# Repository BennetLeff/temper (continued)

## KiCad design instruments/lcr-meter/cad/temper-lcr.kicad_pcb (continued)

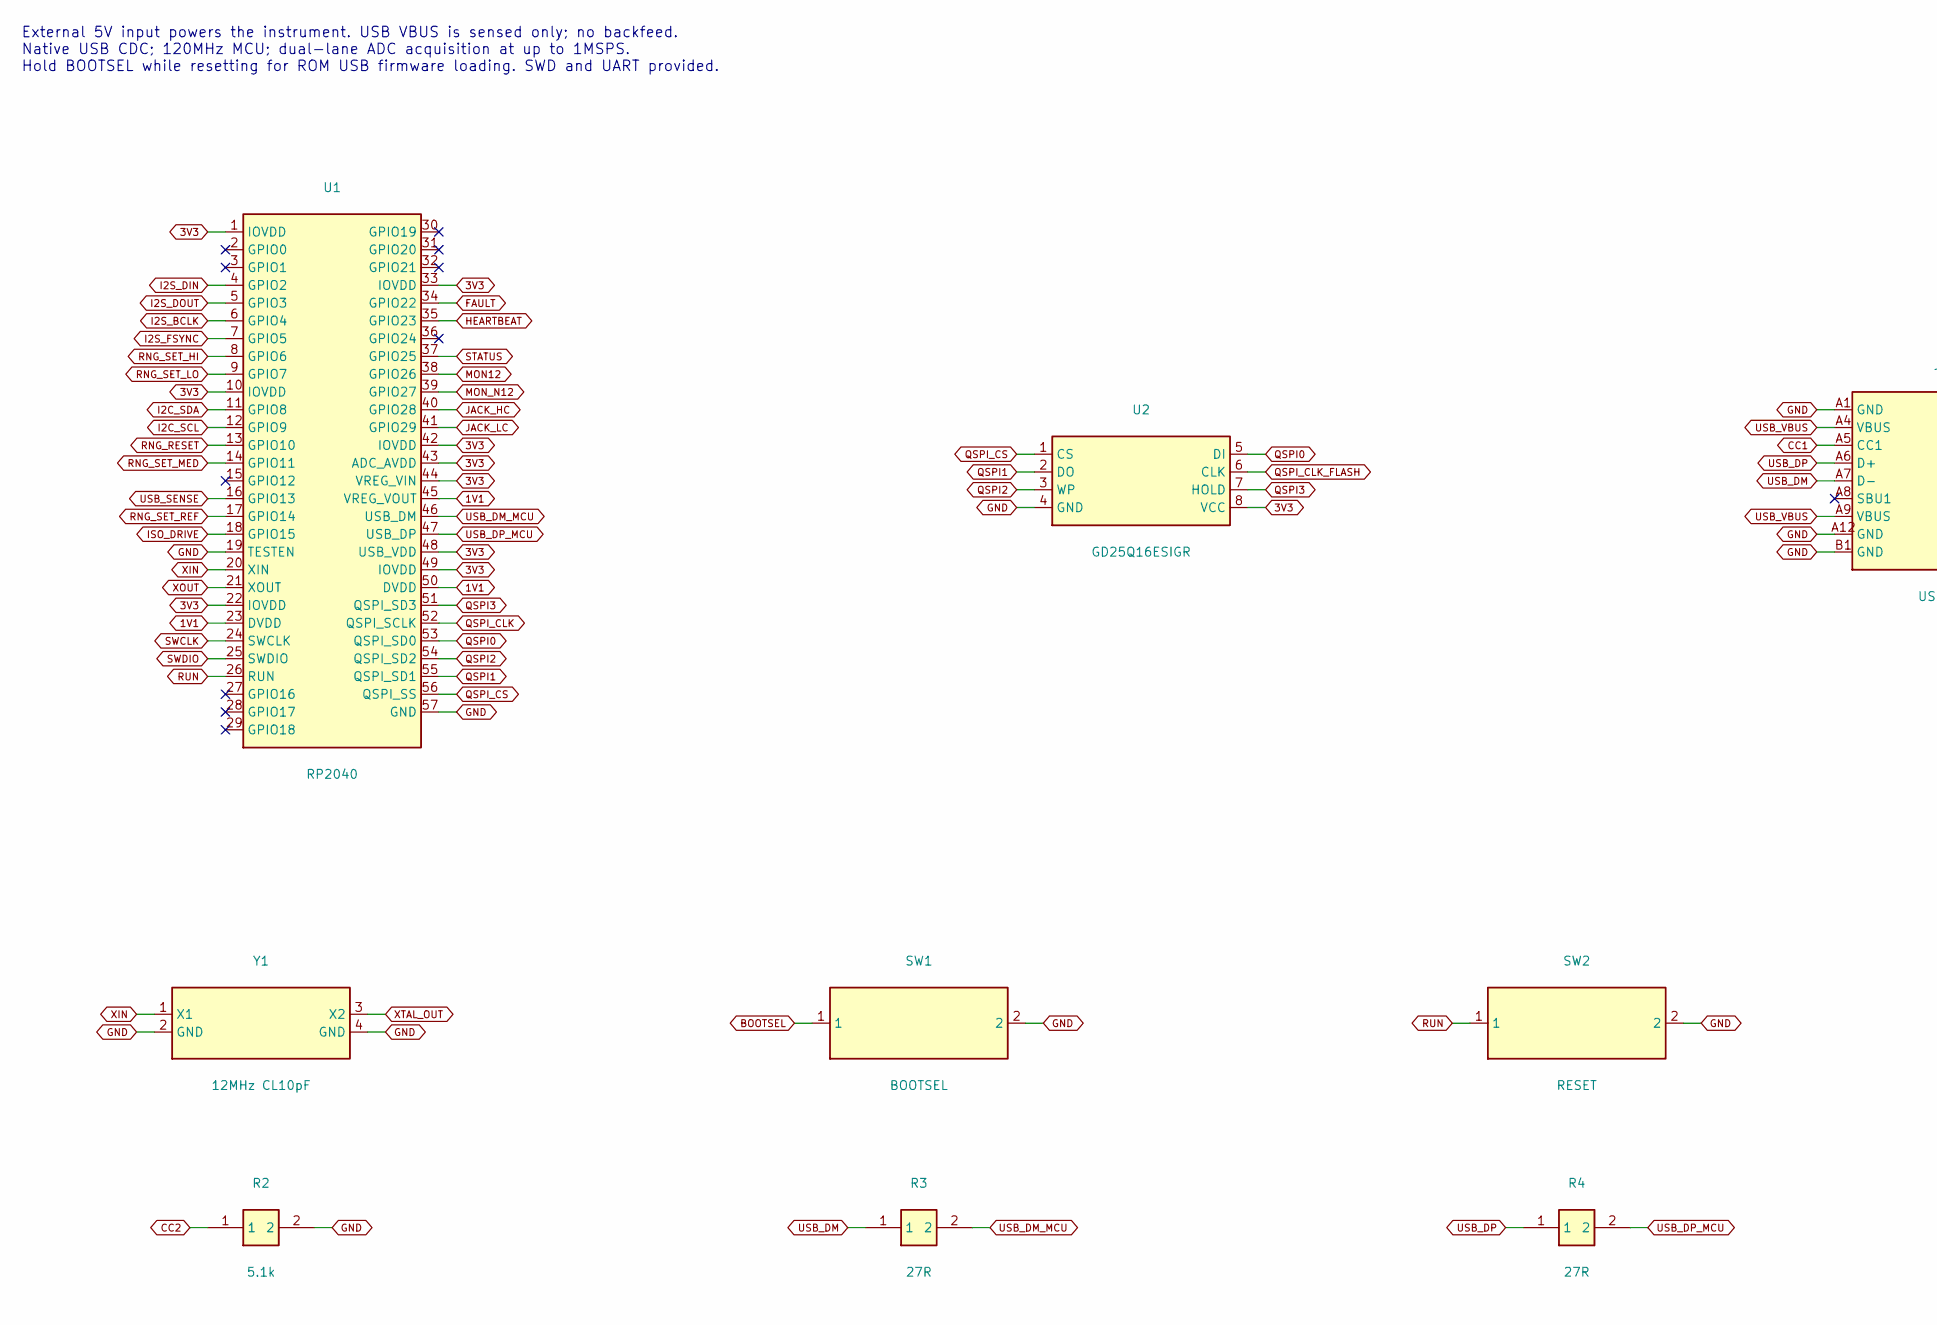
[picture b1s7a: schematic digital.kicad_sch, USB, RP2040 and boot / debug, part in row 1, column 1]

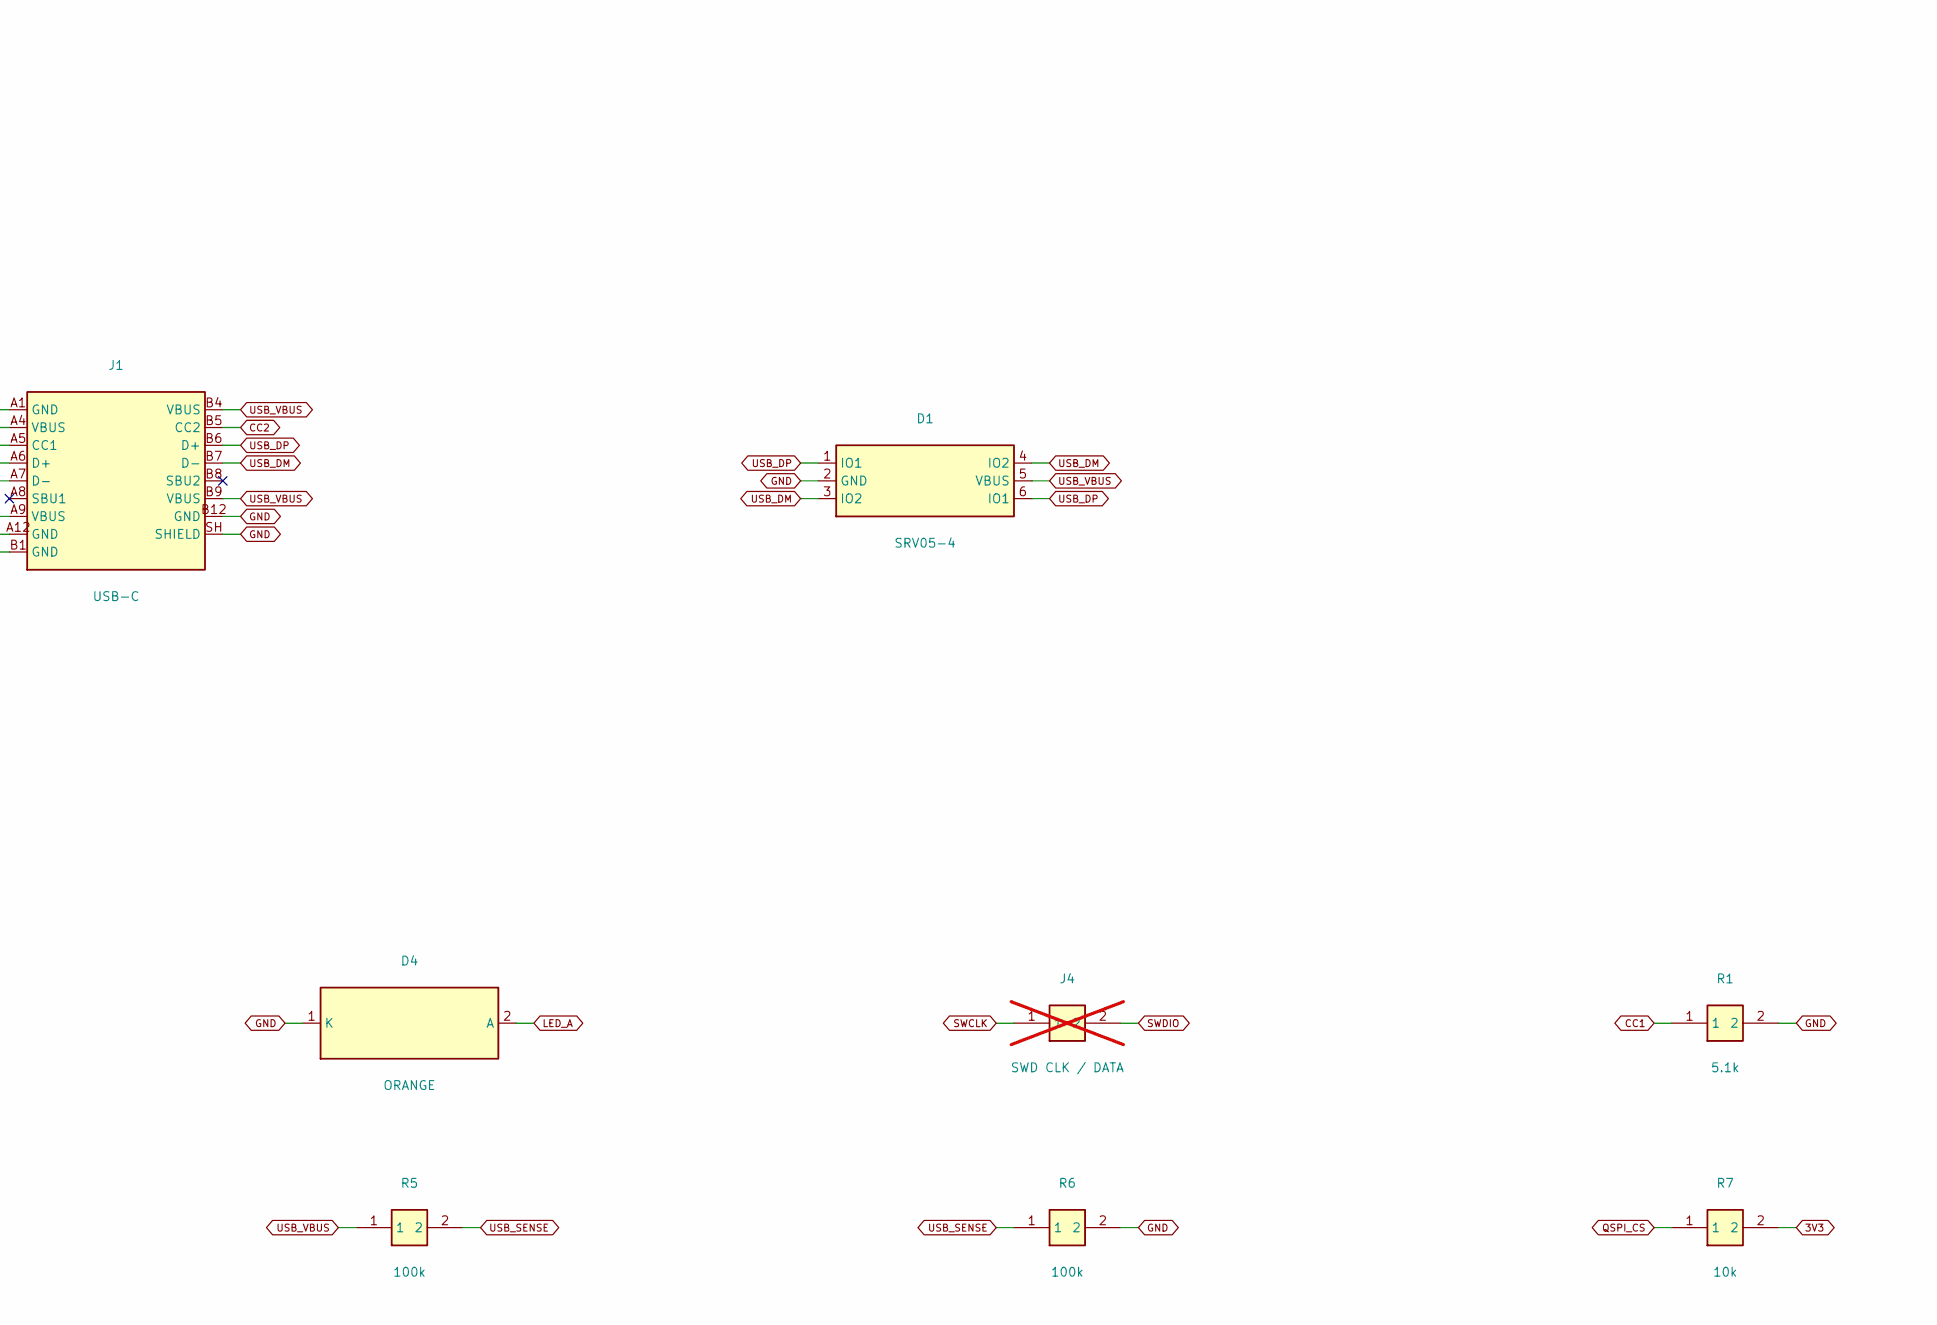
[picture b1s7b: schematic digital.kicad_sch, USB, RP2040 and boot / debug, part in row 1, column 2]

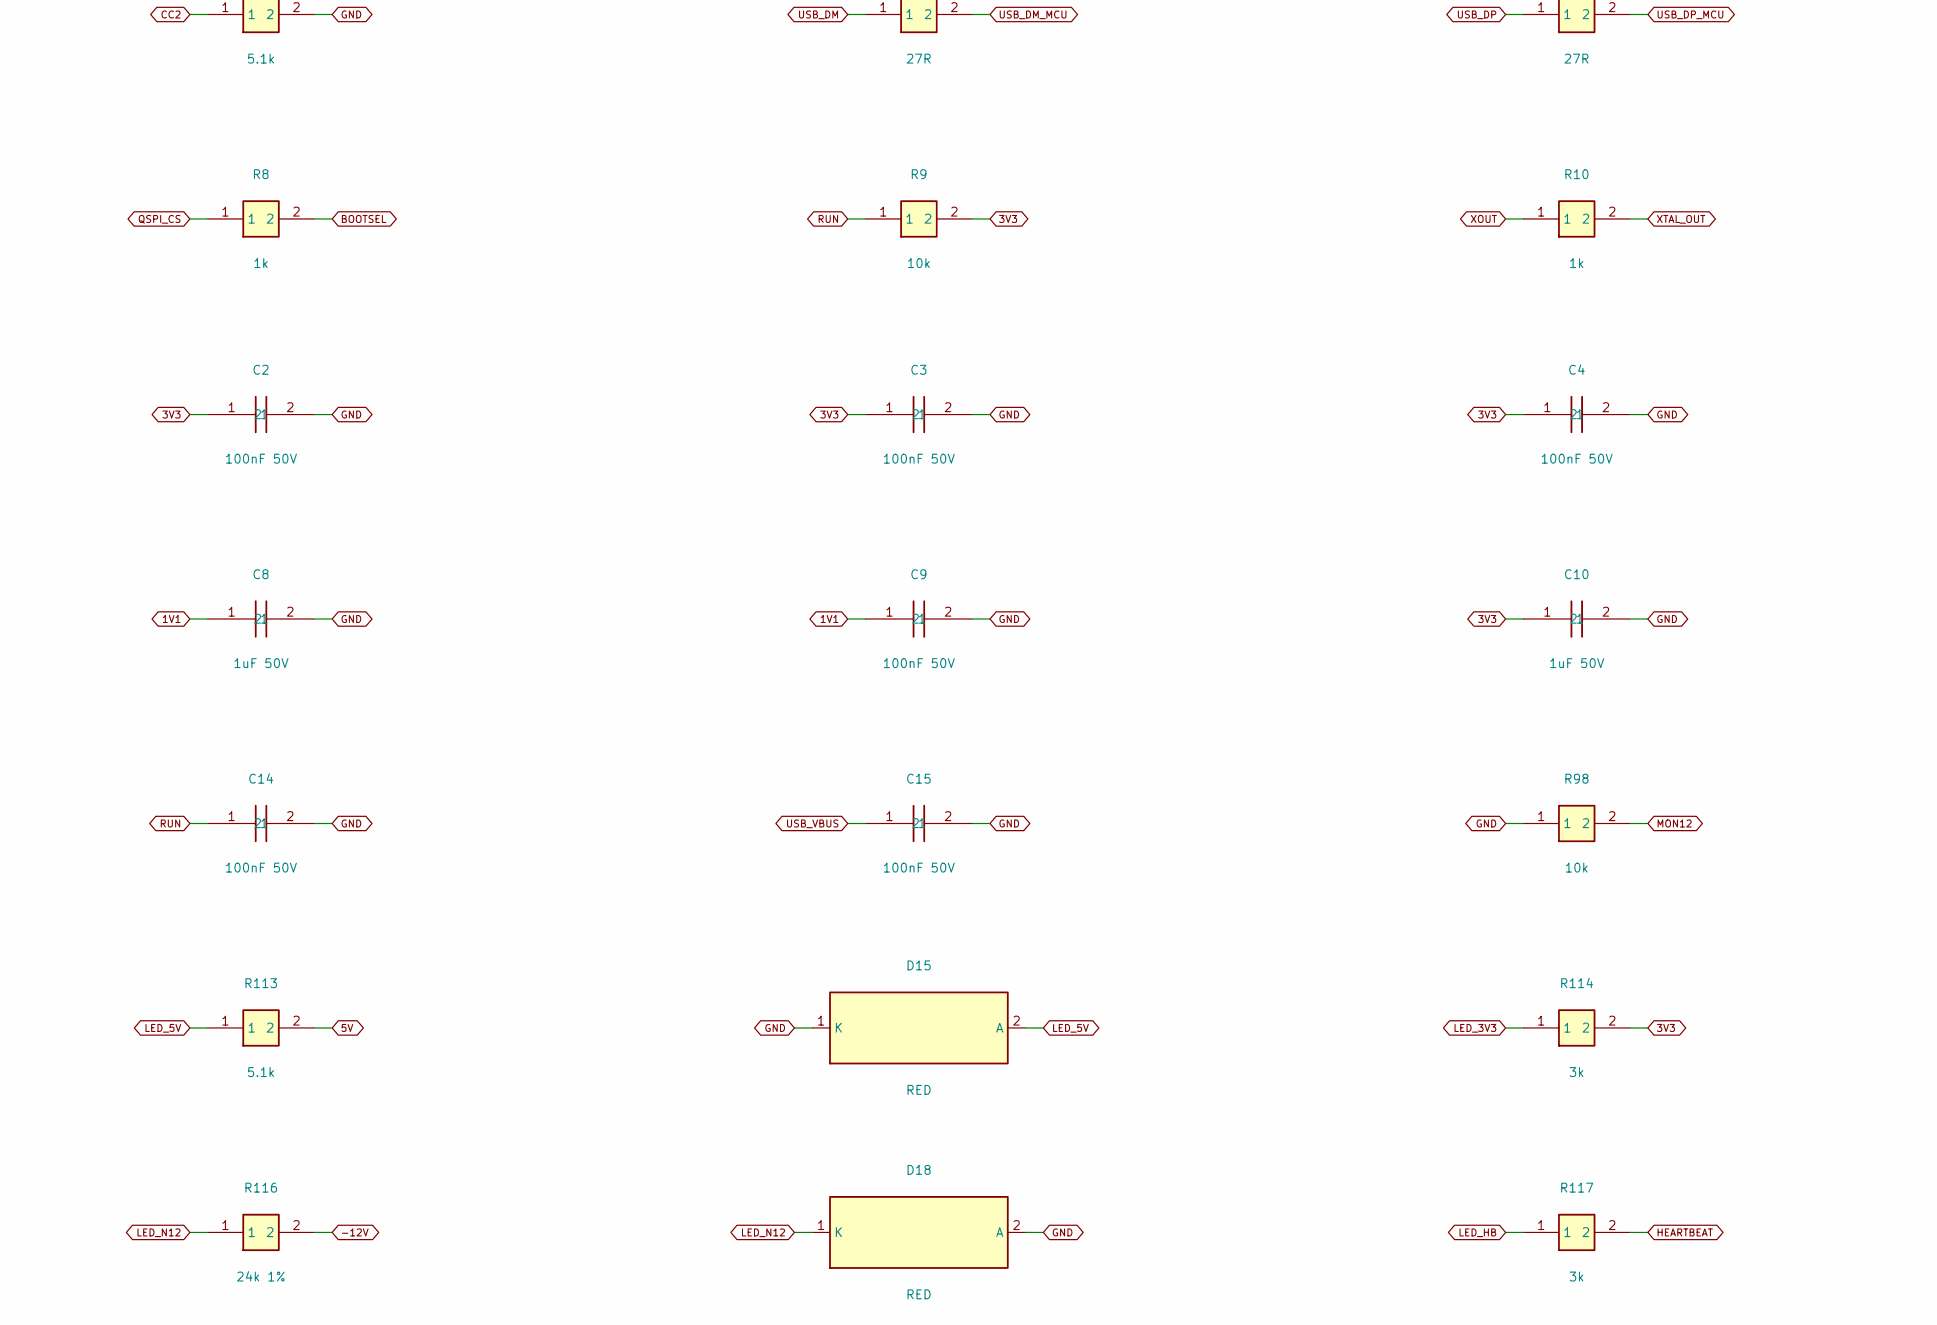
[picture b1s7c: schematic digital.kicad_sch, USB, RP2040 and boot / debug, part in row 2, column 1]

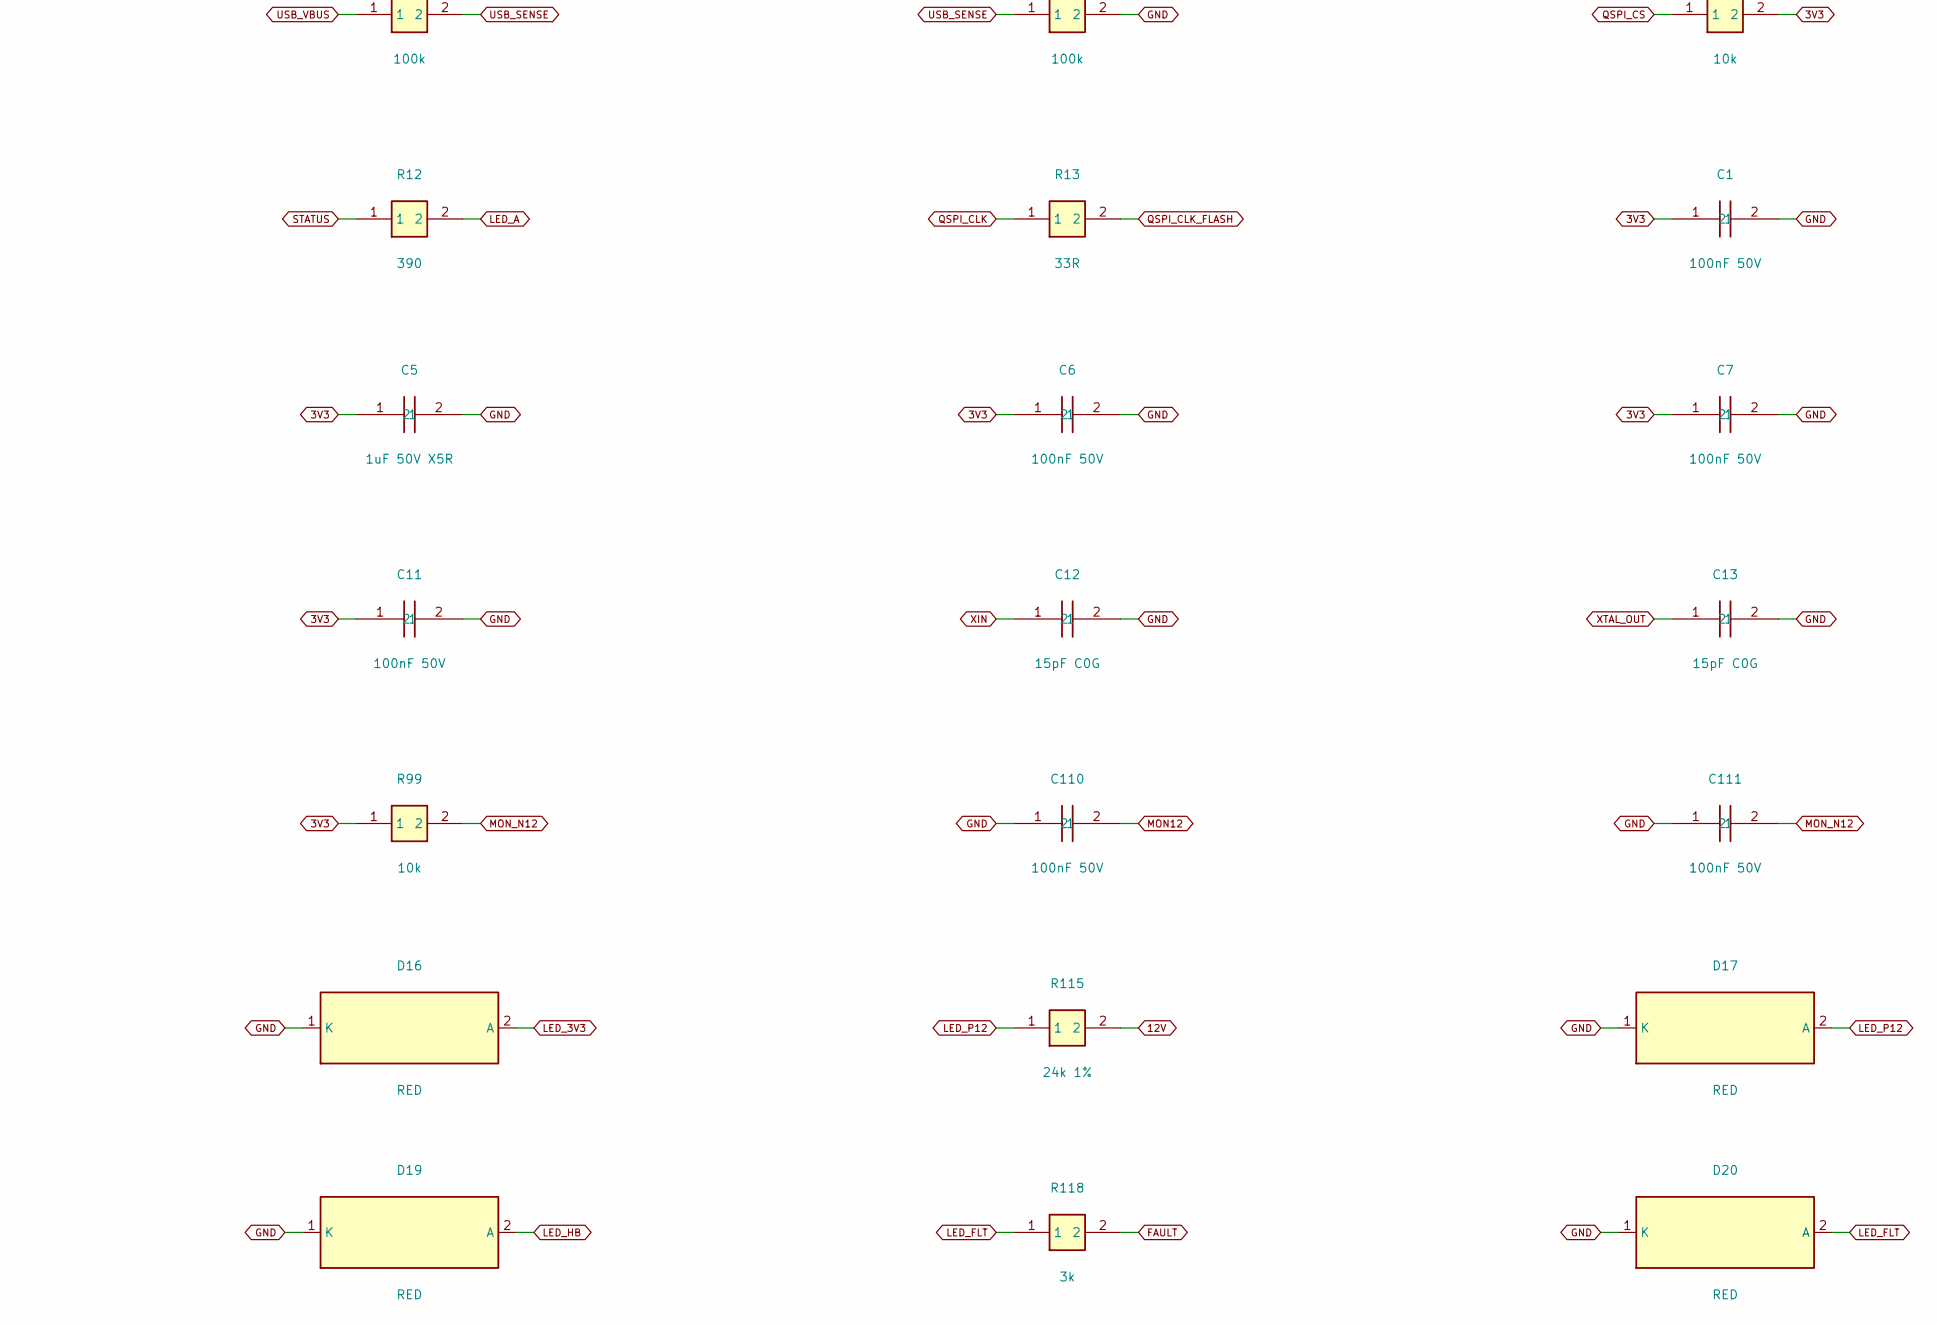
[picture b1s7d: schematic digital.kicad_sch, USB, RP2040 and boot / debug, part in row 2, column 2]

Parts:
C1, C2, C3, C4, C6, C7, C9, C11, C14, C15, C110, C111: 100nF 50V; C_0603_1608Metric; MPN CC0603KRX7R9BB104; LCSC C14663
C5: 1uF 50V X5R; C_0603_1608Metric; MPN CL10A105KB8NNNC; LCSC C15849
C8, C10: 1uF 50V; C_0805_2012Metric; MPN CL21B105KBFNNNE; LCSC C28323
C12, C13: 15pF C0G; C_0603_1608Metric; MPN CL10C150JB8NNNC; LCSC C1644
D1: SRV05-4; SOT-23-6; MPN SRV05-4; LCSC C7420376
D4: ORANGE; LED_LiteOn_LTST-S270KFKT_SideView; MPN LTST-S270KFKT; LCSC C160472
D15, D16, D17, D18, D19, D20: RED; LED_0603_1608Metric; MPN KT-0603R; LCSC C2286
J1: USB-C; USB_C_Receptacle_HRO_TYPE-C-31-M-12; MPN TYPE-C-31-M-12; LCSC C165948
J4: SWD CLK / DATA; PinHeader_1x02_P2.54mm_Vertical; MPN TSW-102-07-G-S; LCSC C7402729; not fitted
R1, R2, R113: 5.1k; R_0603_1608Metric; MPN 0603WAF5101T5E; LCSC C23186
R3, R4: 27R; R_0603_1608Metric; MPN 0603WAF270JT5E; LCSC C25190
R5, R6: 100k; R_0603_1608Metric; MPN 0603WAF1003T5E; LCSC C25803
R7, R9, R98, R99: 10k; R_0603_1608Metric; MPN 0603WAF1002T5E; LCSC C25804
R8, R10: 1k; R_0603_1608Metric; MPN 0603WAF1001T5E; LCSC C21190
R12: 390; R_0603_1608Metric; MPN 0603WAF3900T5E; LCSC C23151
R13: 33R; R_0603_1608Metric; MPN 0603WAF330JT5E; LCSC C23140
R114, R117, R118: 3k; R_0603_1608Metric; MPN 0603WAF3001T5E; LCSC C4211
R115, R116: 24k 1%; R_0603_1608Metric; MPN 0603WAF2402T5E; LCSC C23352
SW1: BOOTSEL; SW_SPST_TS-1088-xR020; MPN TS-1088-AR02016; LCSC C720477
SW2: RESET; SW_SPST_TS-1088-xR020; MPN TS-1088-AR02016; LCSC C720477
U1: RP2040; QFN-56-1EP_7x7mm_P0.4mm_EP3.2x3.2mm; MPN RP2040; LCSC C2040
U2: GD25Q16ESIGR; SOIC-8_5.3x5.3mm_P1.27mm; MPN GD25Q16ESIGR; LCSC C2922792
Y1: 12MHz CL10pF; Crystal_SMD_3225-4Pin_3.2x2.5mm; MPN ABM8-272-T3; LCSC C20625731

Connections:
1V1: C8.1, C9.1, U1.23 (DVDD), U1.45 (VREG_VOUT), U1.50 (DVDD)
3V3: C1.1, C2.1, C3.1, C4.1, C5.1, C6.1, C7.1, C10.1, C11.1, R7.2, R9.2, R99.1, R114.2, U1.1 (IOVDD), U1.10 (IOVDD), U1.22 (IOVDD), U1.33 (IOVDD), U1.42 (IOVDD), U1.43 (ADC_AVDD), U1.44 (VREG_VIN), U1.48 (USB_VDD), U1.49 (IOVDD), U2.8 (VCC); also elsewhere on the board
5V: R113.2; also elsewhere on the board
12V: R115.2; also elsewhere on the board
-12V: R116.2; also elsewhere on the board
BOOTSEL: R8.2, SW1.1
CC1: J1.A5 (CC1), R1.1
CC2: J1.B5 (CC2), R2.1
FAULT: R118.2, U1.34 (GPIO22)
GND: C1.2, C2.2, C3.2, C4.2, C5.2, C6.2, C7.2, C8.2, C9.2, C10.2, C11.2, C12.2, C13.2, C14.2, C15.2, C110.1, C111.1, D1.2 (GND), D4.1 (K), D15.1 (K), D16.1 (K), D17.1 (K), D18.2 (A), D19.1 (K), D20.1 (K), J1.A1 (GND), J1.A12 (GND), J1.B1 (GND), J1.B12 (GND), J1.SH (SHIELD), R1.2, R2.2, R6.2, R98.1, SW1.2, SW2.2, U1.19 (TESTEN), U1.57 (GND), U2.4 (GND), Y1.2 (GND), Y1.4 (GND); also elsewhere on the board
HEARTBEAT: R117.2, U1.35 (GPIO23)
I2C_SCL: U1.12 (GPIO9); also elsewhere on the board
I2C_SDA: U1.11 (GPIO8); also elsewhere on the board
I2S_BCLK: U1.6 (GPIO4); also elsewhere on the board
I2S_DIN: U1.4 (GPIO2); also elsewhere on the board
I2S_DOUT: U1.5 (GPIO3); also elsewhere on the board
I2S_FSYNC: U1.7 (GPIO5); also elsewhere on the board
ISO_DRIVE: U1.18 (GPIO15); also elsewhere on the board
JACK_HC: U1.40 (GPIO28); also elsewhere on the board
JACK_LC: U1.41 (GPIO29); also elsewhere on the board
LED_3V3: D16.2 (A), R114.1
LED_5V: D15.2 (A), R113.1
LED_A: D4.2 (A), R12.2
LED_FLT: D20.2 (A), R118.1
LED_HB: D19.2 (A), R117.1
LED_N12: D18.1 (K), R116.1
LED_P12: D17.2 (A), R115.1
MON12: C110.2, R98.2, U1.38 (GPIO26); also elsewhere on the board
MON_N12: C111.2, R99.2, U1.39 (GPIO27); also elsewhere on the board
QSPI0: U1.53 (QSPI_SD0), U2.5 (DI)
QSPI1: U1.55 (QSPI_SD1), U2.2 (DO)
QSPI2: U1.54 (QSPI_SD2), U2.3 (WP)
QSPI3: U1.51 (QSPI_SD3), U2.7 (HOLD)
QSPI_CLK: R13.1, U1.52 (QSPI_SCLK)
QSPI_CLK_FLASH: R13.2, U2.6 (CLK)
QSPI_CS: R7.1, R8.1, U1.56 (QSPI_SS), U2.1 (CS)
RNG_RESET: U1.13 (GPIO10); also elsewhere on the board
RNG_SET_HI: U1.8 (GPIO6); also elsewhere on the board
RNG_SET_LO: U1.9 (GPIO7); also elsewhere on the board
RNG_SET_MED: U1.14 (GPIO11); also elsewhere on the board
RNG_SET_REF: U1.17 (GPIO14); also elsewhere on the board
RUN: C14.1, R9.1, SW2.1, U1.26 (RUN)
STATUS: R12.1, U1.37 (GPIO25)
SWCLK: J4.1, U1.24 (SWCLK)
SWDIO: J4.2, U1.25 (SWDIO)
USB_DM: D1.3 (IO2), D1.4 (IO2), J1.A7 (D-), J1.B7 (D-), R3.1
USB_DM_MCU: R3.2, U1.46 (USB_DM)
USB_DP: D1.1 (IO1), D1.6 (IO1), J1.A6 (D+), J1.B6 (D+), R4.1
USB_DP_MCU: R4.2, U1.47 (USB_DP)
USB_SENSE: R5.2, R6.1, U1.16 (GPIO13)
USB_VBUS: C15.1, D1.5 (VBUS), J1.A4 (VBUS), J1.A9 (VBUS), J1.B4 (VBUS), J1.B9 (VBUS), R5.1; also elsewhere on the board
XIN: C12.1, U1.20 (XIN), Y1.1 (X1)
XOUT: R10.1, U1.21 (XOUT)
XTAL_OUT: C13.1, R10.2, Y1.3 (X2)

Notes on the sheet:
External 5V input powers the instrument. USB VBUS is sensed only; no backfeed. Native USB CDC; 120MHz MCU; dual-lane ADC acquisition at up to 1MSPS. Hold BOOTSEL while resetting for ROM USB firmware loading. SWD and UART provided.
